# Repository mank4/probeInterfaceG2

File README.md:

# probeInterfaceG2

probeInterfaceG2 is a USB controlled interface box for transmission and reception of digital signals on 12-pins of a 14-pin flat band cable. The pin number layout is common with [GGB Picoprobe multi-contact wedge probes](https://ggb.com/home/multi-contact-wedges/). It features galvanically isolated USB for control, adjustable logic levels from 0.65 to 3.3 V and relays for disabling unused pins. The device is controlled via IEEE 488.2 compatible SCPI commands.

Currently the following interfaces are supported:
- GPIO
- SPI

probeInterfaceG2 is licensed under GPL v3. As the case's 3D model is assumed to be (c) Hammond Manufacturing Ltd., originally obtained from https://www.hammfg.com/electronics/small-case/extruded/1455#product-tables, a script is included to download the model.

probeInterfaceG2 uses
- [tinyusb](https://github.com/hathach/tinyusb)
- [scpi-parser](https://github.com/j123b567/scpi-parser)

## Hardware Features

- Raspberry RP2040 microcontroller
  - pio cells for high-speed, unconstraint muxable IO functions
  - integrated USB for programming and IEEE 488.2 SCPI control
- 0.65V - 3.3V level shifters
  - Controllable common logic level by discrete 12-bit R-2R DAC or external input
- Relays for enabling/disabling IOs

## SCPI commands

Pin numbering is based on [GGB Picoprobe multi-contact wedge probes](https://ggb.com/home/multi-contact-wedges/) numbering scheme.

__*IDN?__

Returns device type.

__*RST__

Resets settings made and clears error.

__*CLS__

Clears error. Device stores only a single error.

__:SYSTem:ERRor[:NEXT]?__

Returns <errorNumber>,<errorDescription> as described by [Keysight](https://na.support.keysight.com/pna/help/latest/Support/SCPI_Errors.htm) and clears error.

__:SYSTem:ERRor:COUNt?__

Returns number of errors.

__:SYSTem:VERSion?__

Returns system version number.

__ECHO `<text>`__

Echos argument.

__BOOTSEL__

Reboots the pin in bootloader mode.

__IO:LEVel `<V>`__

Sets the IO level voltage.

__IO<1:12>:FUnc `<IN|OUT|CS|SCK|MISO|MOSI>`__

Sets the pins function to one of the following. IN and OUT can be used multiple times while the SPI related functions can only be used once. Pins are left in last configuration when changing SPI related functions from one pin to another. This function does not enable the according output relay.

__IO<1:12>:ENable <1|0>__

Enables or disables the relay of the corresponding IO pin.

__IO<1:12>:WRite <1|0>__

Sets an OUT configured pin high or low.

__IO<1:12>:REad__

Reads an IN configured pin and returns 0 or 1.

__SPI:TRANSfer? <binary values>__

Writes the given bytes to the SPI bus using the configured settings and returns the response of MISO as binary values.

__SPI:CPHA <1|0>__

Sets the Clock phase (CPHA) to the corresponding value.

__SPI:CPOL <1|0>__

Sets the Clock polarity (CPOL) to the corresponding value.

__SPI:BAUDrate <MHz>__

Speed of the probes SPI interface is set to defined float value in MHz.

__SPI:BAUDrate?__

Reads the speed of the currently configured baudrate as float in MHz.

## RP2040 toolchain

Assuming Windows or Ubuntu/Debian the following setup is required for compiling the firmware. For normal use this is not required, VISA drivers (on Windows) are sufficient for common use.

- Only on windows: Install WSL / Ubuntu on Windows, run `sudo apt update`
- Make sure the following packages exist: `sudo apt install cmake gcc-arm-none-eabi libnewlib-arm-none-eabi libstdc++-arm-none-eabi-newlib git build-essential`
- Clone dependencies: `git submodule init` and `git submodule update`
- Clone the [pico-sdk](https://github.com/raspberrypi/pico-sdk) into the same folder as probeInterfaceG2 and update submodules if requested by cmake in the next steps
- Create build folder in firmware and cd into. `cd fw && mkdir build && cd build`
- Then run `export PICO_SDK_PATH=../../../pico-sdk` and `cmake ..`
- Then `make -j4` (4 is the number of cores used for compilation)
- If compilation fails with USB descriptor length errors, do the following: cd into pico-sdk folder and `cd lib/tinyusb/` and then `git pull origin master`
- On Windows and Linux: Copy the uf2 onto the mass storage of the RP2040. Bootloader mode is entered by pressing the button while plugging in.
- With correctly set up udev rules: Run `../load.sh` with the RP2040 connected via USB. When not running the probeInterfaceG2 firmware ress the button while pluggin in. [udev rules](https://gist.github.com/alejoseb/c7a7b4c67f0cf665dadabb26a5a87597) for the probeInterfaceG2:
```
/etc/udev/rules.d/99-probeInterfaceG2.rules
SUBSYSTEMS=="usb", ACTION=="add", ATTRS{idVendor}=="16c0", ATTRS{idProduct}=="03e8",  MODE="0666", GROUP="usbtmc"
```

For programming hints see the [Getting started](https://datasheets.raspberrypi.com/pico/getting-started-with-pico.pdf) guide.

## Possible improvements

- Better 3.3 V overvoltage protection circuit currently realized using X0202NN
- Ethernet interface VXI11
- Integrated power supply for DUT, with high precision measurement functions and grounding feature

## Resources

- Frontend
  - Agilent E3631 Service Guide
  - HP 6114A Service Guide
  - Power Designs 5020 Service Guide
  - The Art of Electronics by Horowitz
- Microcontroller
  - [RP2040](https://www.raspberrypi.com/documentation/microcontrollers/rp2040.html), [Pi pico](https://www.raspberrypi.com/products/raspberry-pi-pico/), RP2040 Minimal Kicad reference design
  - [SCPI specifications](https://www.ivifoundation.org/specifications/default.aspx), [SCPI-99 standard](https://www.ivifoundation.org/docs/scpi-99.pdf), [SCPI library](https://github.com/j123b567/scpi-parser)
  - [tinyusb for usbtmc](https://github.com/hathach/tinyusb), [example](https://github.com/markb139/pico_logic)
- Ethernet
  - Wiznet w5500 [eval](https://www.wiznet.io/product-item/w5500-evb-pico/) [doc](https://docs.wiznet.io/Product/iEthernet/W5500/w5500-evb-pico)

## Acknowledgement

The financial support by the Federal Ministry of Education and Research of Germany in the project "Open6GHub" (grant number: 16KISK005) is acknowledged.

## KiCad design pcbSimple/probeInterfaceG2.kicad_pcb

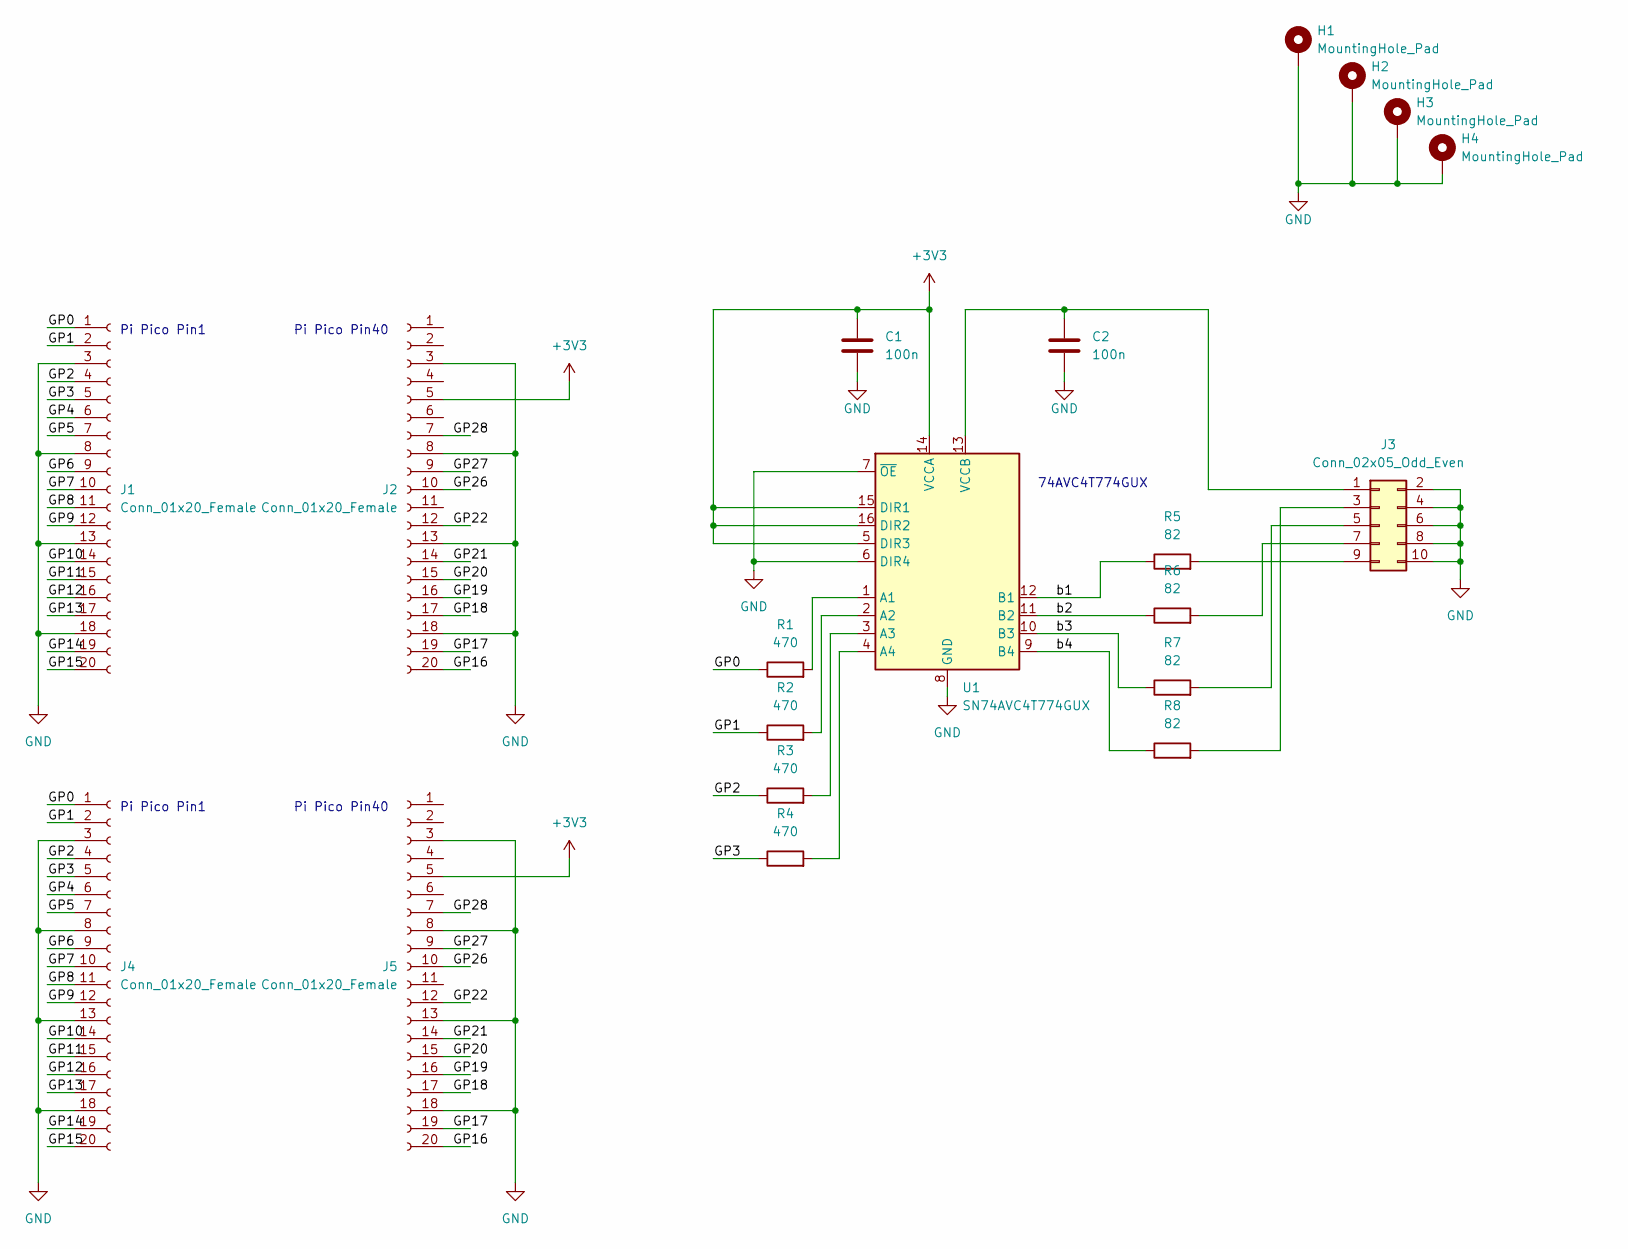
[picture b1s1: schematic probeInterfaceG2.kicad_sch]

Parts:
C1, C2: 100n; C_0402_1005Metric
H1, H2, H3, H4: MountingHole_Pad; MountingHole_3.2mm_M3_DIN965_Pad
J1, J2, J4, J5: Conn_01x20_Female; PinSocket_1x20_P2.54mm_Vertical
J3: Conn_02x05_Odd_Even; PinHeader_2x05_P2.54mm_Vertical
R1, R2, R3, R4: 470; R_0402_1005Metric
R5, R6, R7, R8: 82; R_0402_1005Metric
U1: SN74AVC4T774GUX; XQFN16

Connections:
+3V3: C1.1, J2.5, J5.5, U1.5 (DIR3), U1.14 (VCCA), U1.15 (DIR1), U1.16 (DIR2)
/GP0: J1.1, J4.1, R1.1
/GP1: J1.2, J4.2, R2.1
/GP2: J1.4, J4.4, R3.1
/GP3: J1.5, J4.5, R4.1
/GP4: J1.6, J4.6
/GP5: J1.7, J4.7
/GP6: J1.9, J4.9
/GP7: J1.10, J4.10
/GP8: J1.11, J4.11
/GP9: J1.12, J4.12
/GP10: J1.14, J4.14
/GP11: J1.15, J4.15
/GP12: J1.16, J4.16
/GP13: J1.17, J4.17
/GP14: J1.19, J4.19
/GP15: J1.20, J4.20
/GP16: J2.20, J5.20
/GP17: J2.19, J5.19
/GP18: J2.17, J5.17
/GP19: J2.16, J5.16
/GP20: J2.15, J5.15
/GP21: J2.14, J5.14
/GP22: J2.12, J5.12
/GP26: J2.10, J5.10
/GP27: J2.9, J5.9
/GP28: J2.7, J5.7
/b1: R5.1, U1.12 (B1)
/b2: R6.1, U1.11 (B2)
/b3: R7.1, U1.10 (B3)
unnamed: C2.1, J3.1, U1.13 (VCCB)
unnamed: J3.3, R8.2
unnamed: J3.5, R7.2
unnamed: J3.7, R6.2
unnamed: J3.9, R5.2
unnamed: R1.2, U1.1 (A1)
unnamed: R2.2, U1.2 (A2)
unnamed: R3.2, U1.3 (A3)
unnamed: R4.2, U1.4 (A4)

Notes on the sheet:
Pi Pico Pin40
Pi Pico Pin1
74AVC4T774GUX

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
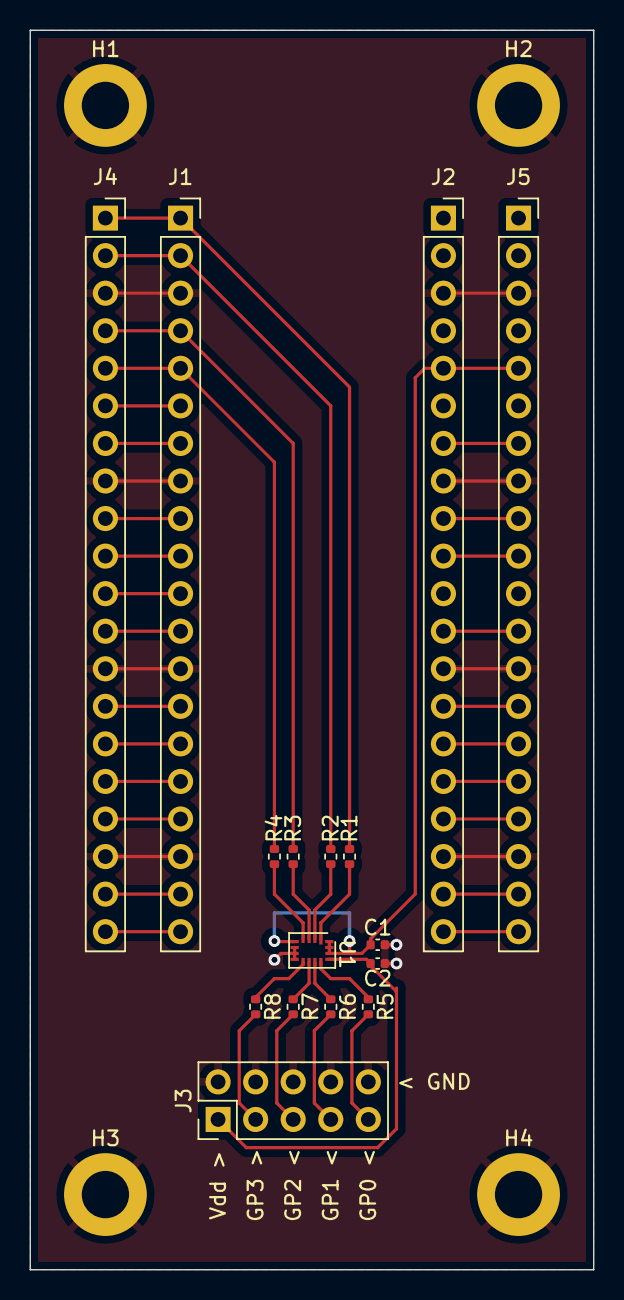
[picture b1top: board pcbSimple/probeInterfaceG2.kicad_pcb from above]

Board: 2 copper layers, 38.1 x 83.8 mm, 20 parts (0 on the bottom side), 41 nets.

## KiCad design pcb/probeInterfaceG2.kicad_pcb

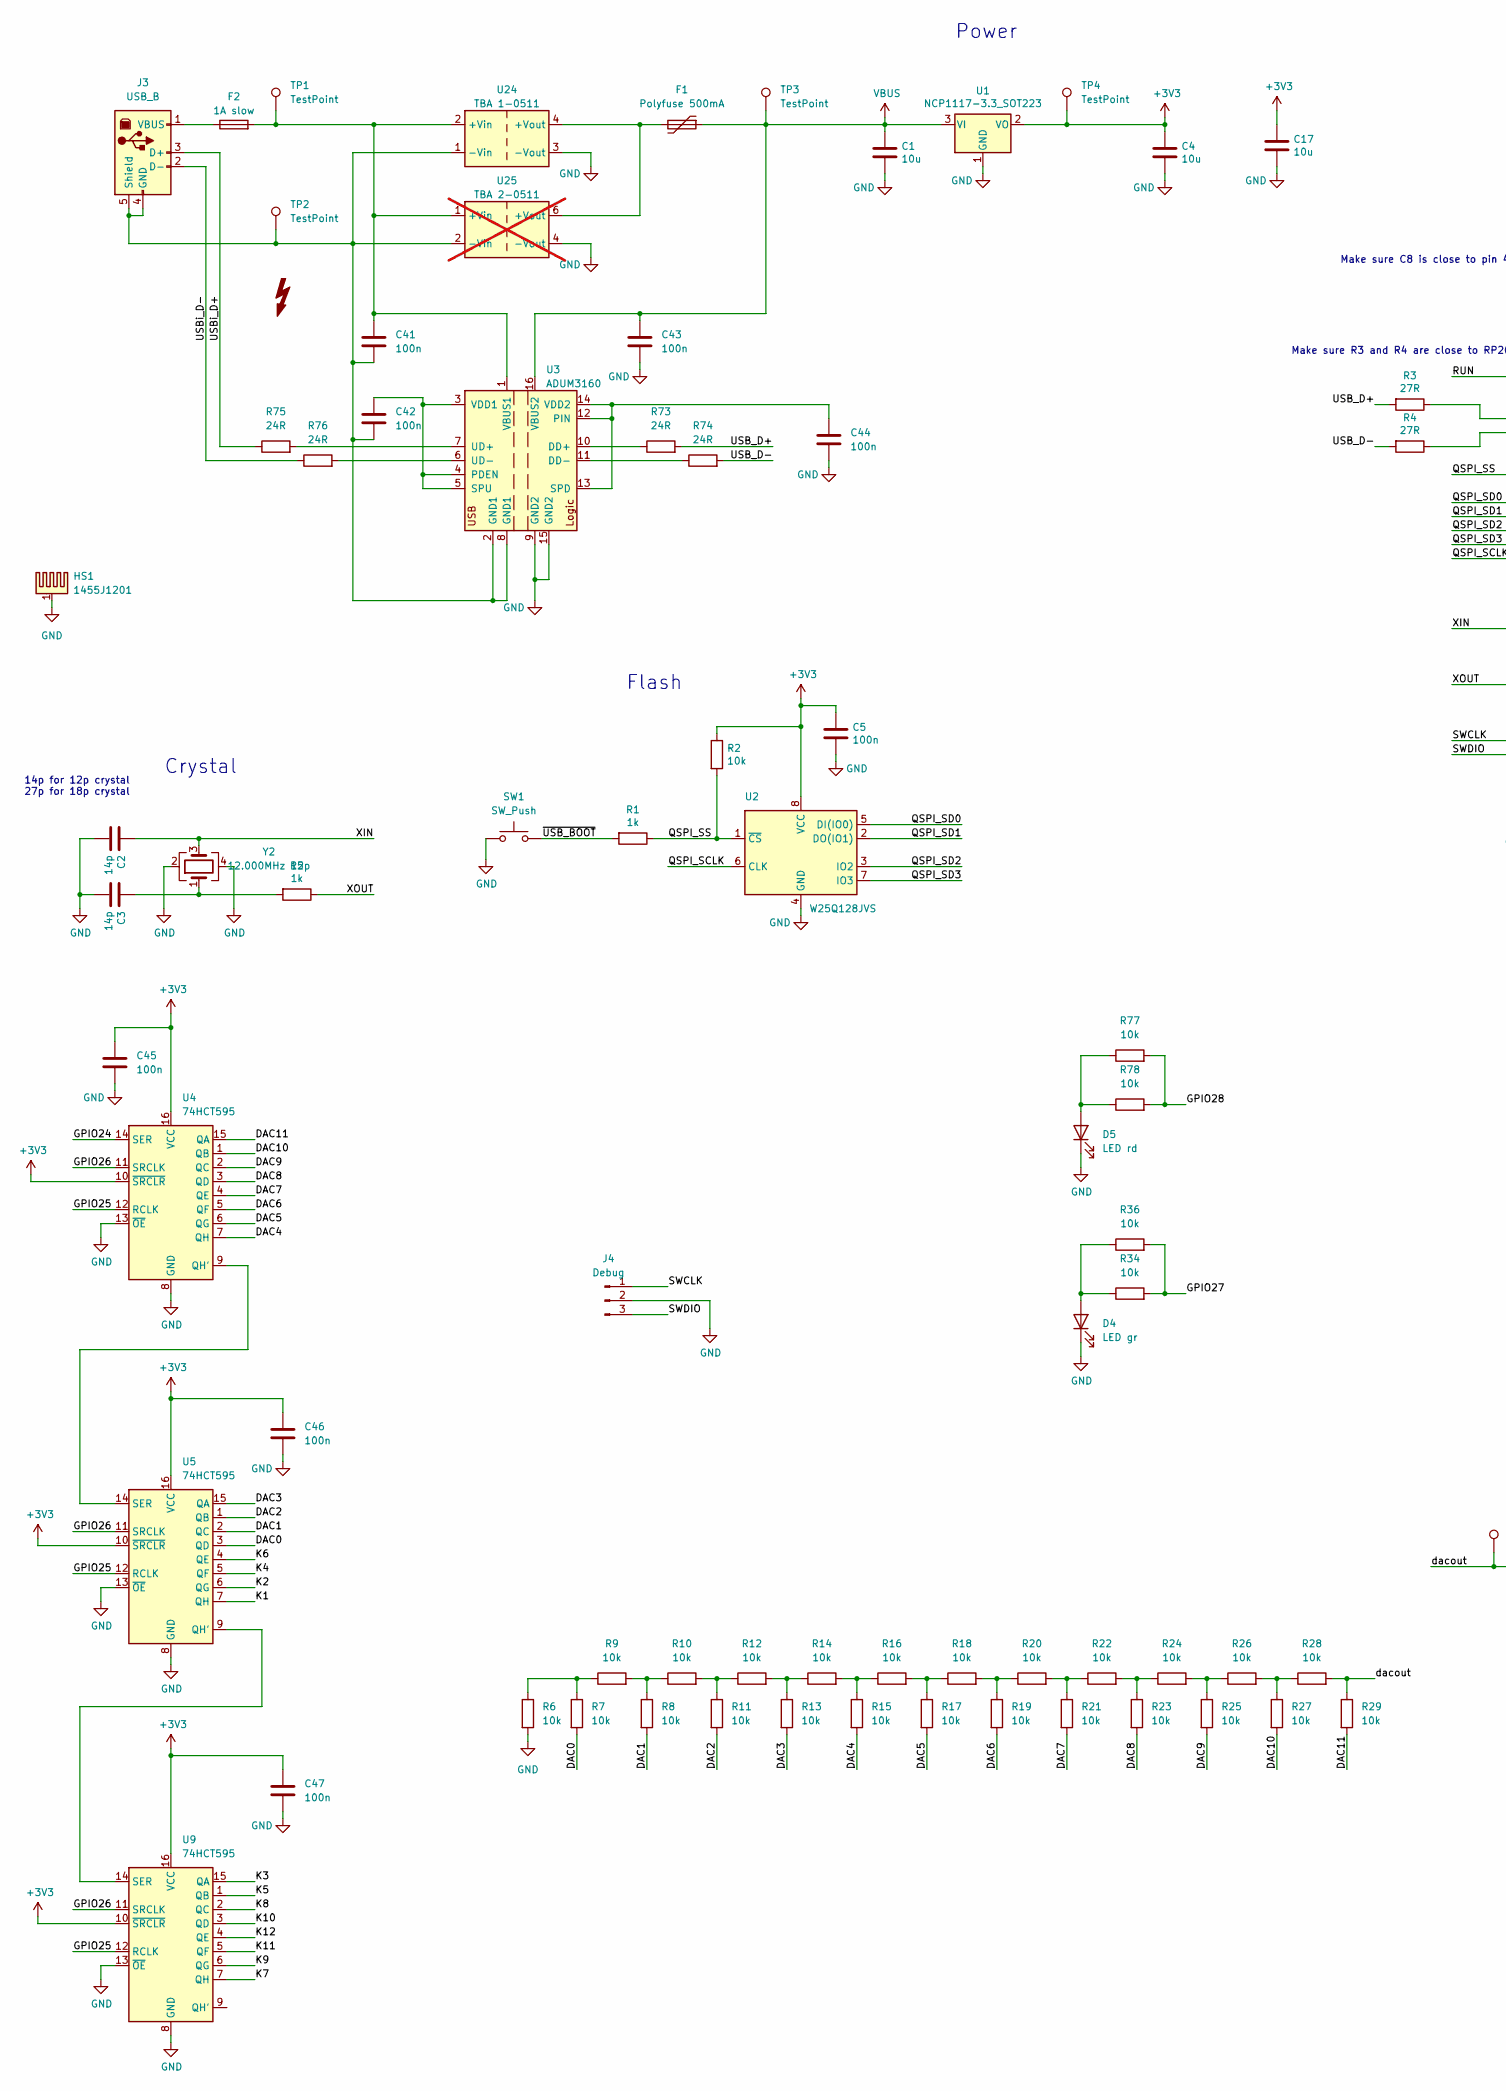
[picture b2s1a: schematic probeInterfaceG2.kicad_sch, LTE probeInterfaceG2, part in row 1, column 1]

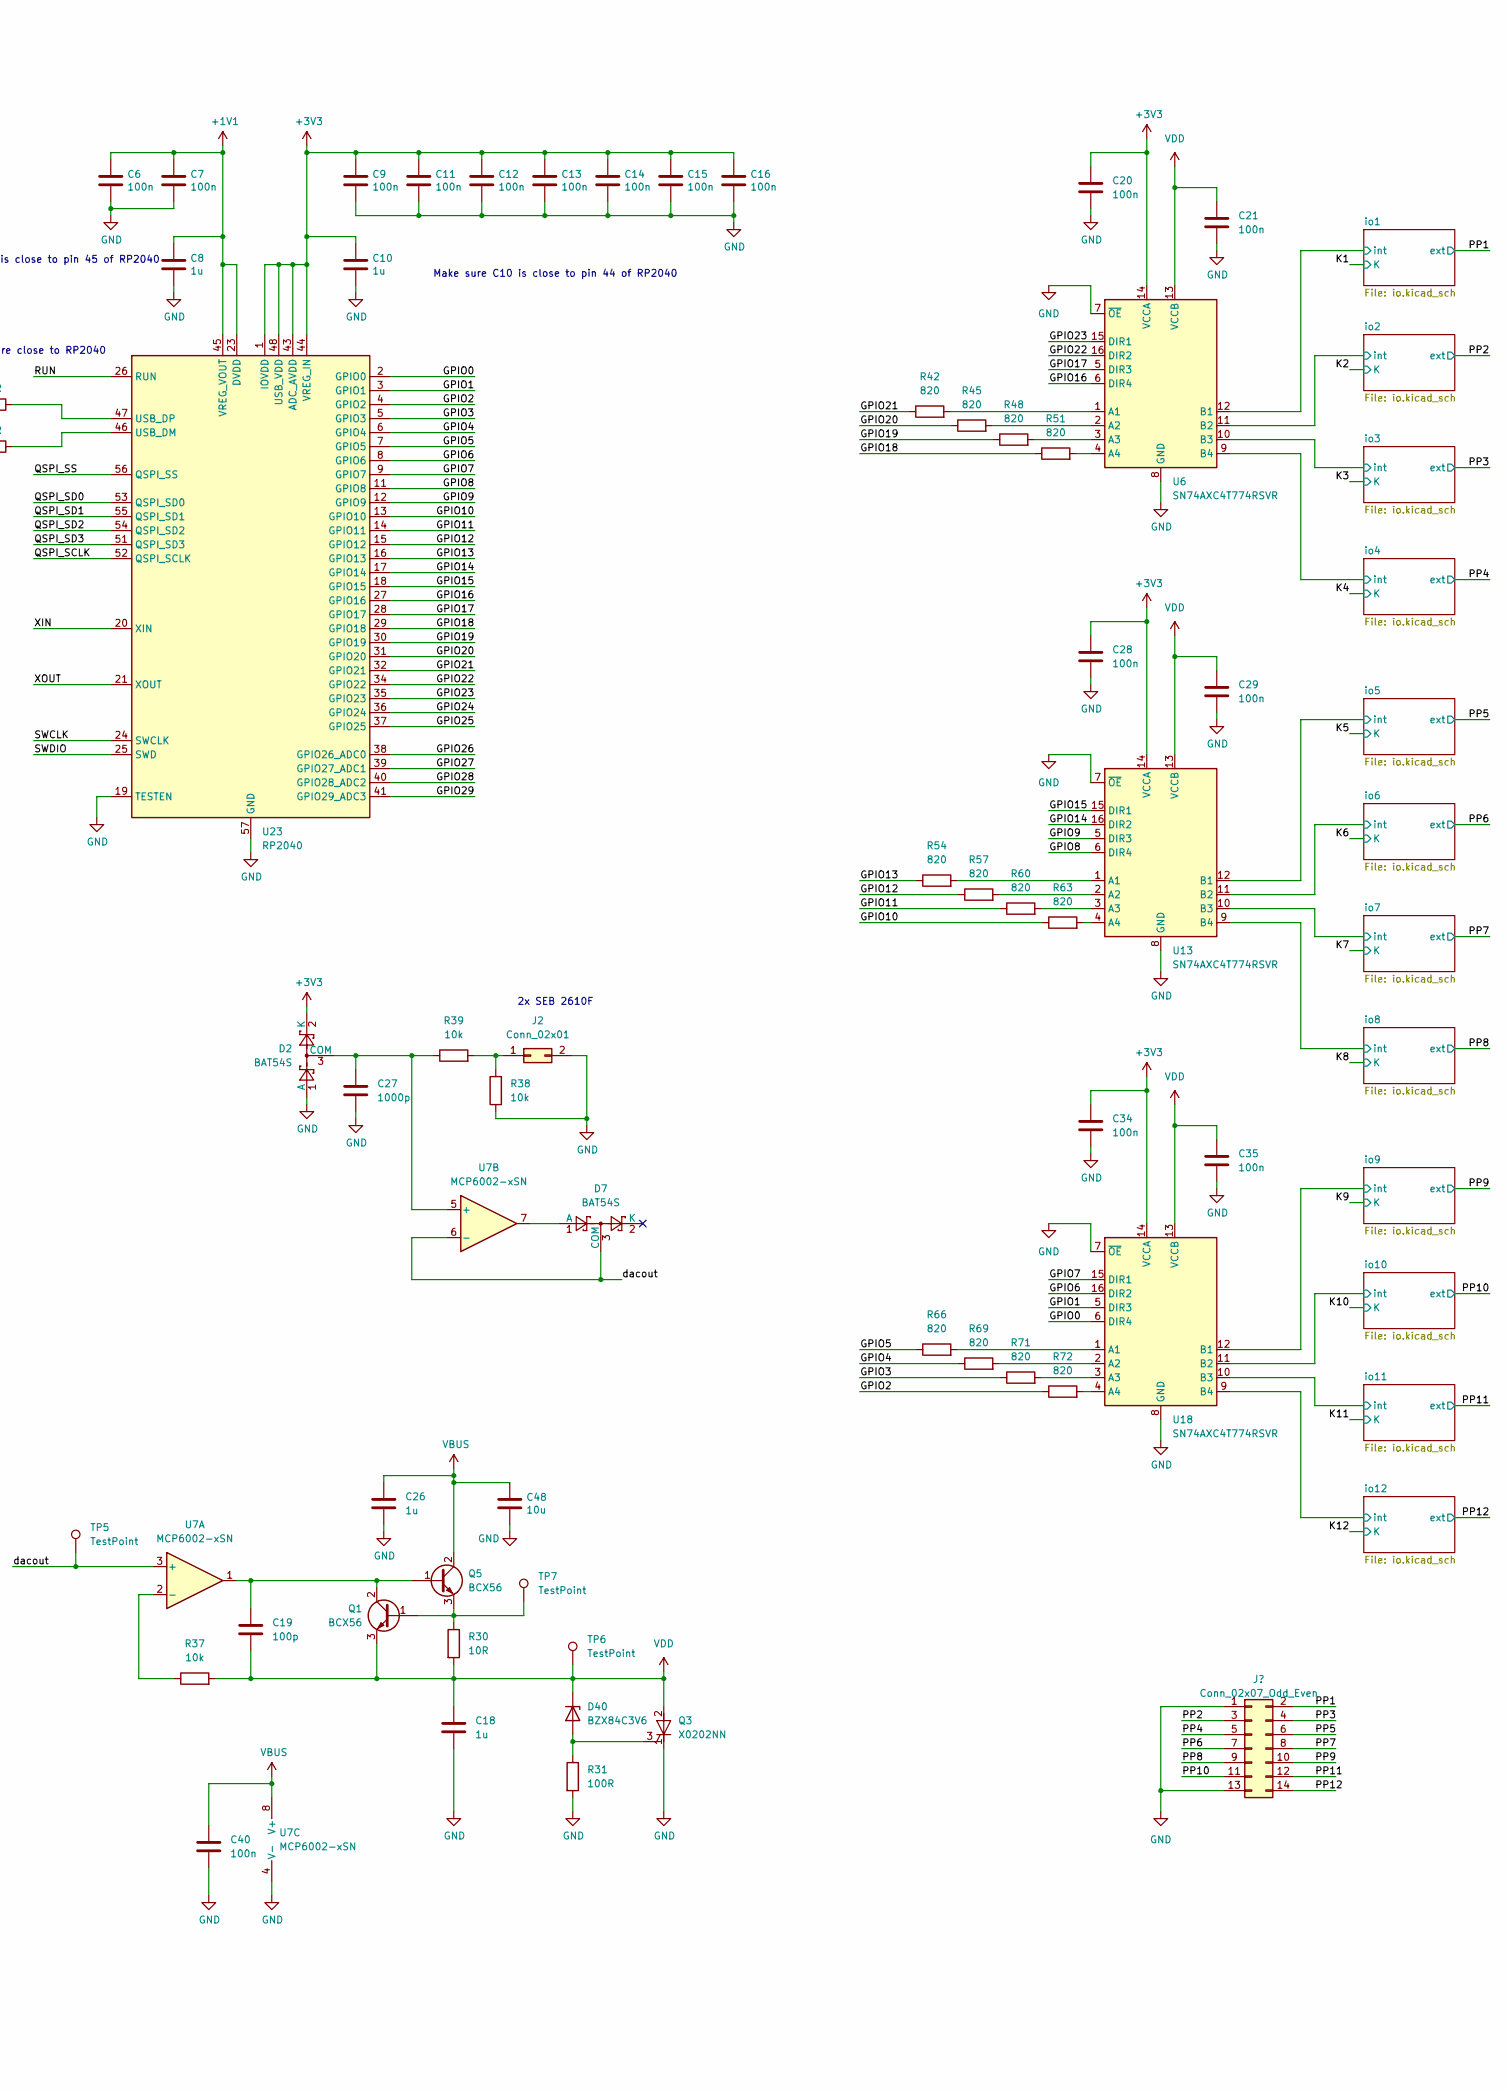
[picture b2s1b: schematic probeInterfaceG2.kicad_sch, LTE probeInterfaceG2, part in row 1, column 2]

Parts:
C1, C4, C17, C48: 10u; C_0805_2012Metric; Digikey 1276-1096-1-ND
C2, C3: 14p; C_0402_1005Metric; Digikey 13-CC0402JPNPO9BN180DKR-ND
C5, C6, C7, C9, C11, C12, C13, C14, C15, C16, C20, C21, C28, C29, C34, C35, C40, C41, C42, C43, C44, C45, C46, C47: 100n; C_0402_1005Metric; Digikey 1276-1043-1-ND
C8, C10, C18, C26: 1u; C_0402_1005Metric; Digikey 1276-1076-1-ND
C19: 100p; C_0402_1005Metric; Digikey 13-CC0402JPNPO9BN101DKR-ND
C27: 1000p; C_0402_1005Metric; Digikey 490-GCM1555C1H102GA16JDKR-ND
D2, D7: BAT54S; SOT-23; Digikey BAT54SLT1GOSDKR-ND
D4: LED gr; LED_0402_1005Metric; Digikey 754-1101-1-ND
D5: LED rd; LED_0402_1005Metric; Digikey 754-1104-1-ND
D40: BZX84C3V6; SOT-23; Digikey BZX84C3V6LT1GOSDKR-ND
F1: Polyfuse 500mA; Fuse_1206_3216Metric; Digikey 0ZCJ0050FF2G
F2: 1A slow; Fuse_1206_3216Metric; Digikey 507-1891-1-ND
HS1: 1455J1201; Digikey HM890-ND
J1: Conn_02x07_Odd_Even; IDC-Header_2x07_P2.54mm_Horizontal; Digikey S9028-ND
J2: Conn_02x01; PinSocket_1x02_P2.54mm_Vertical
J3: USB_B; USB_B_OST_USB-B1HSxx_Horizontal; Digikey 102-3999-ND
J4: Debug; PinHeader_1x03_P2.54mm_Vertical
Q1, Q5: BCX56; SOT-89-3; Digikey 1727-2930-1-ND
Q3: X0202NN; SOT-223; Digikey 497-7697-1-ND
R1, R5: 1k; C_0402_1005Metric; Digikey 13-AC0402FR-131KLDKR-ND
R2, R6, R7, R8, R9, R10, R11, R12, R13, R14, R15, R16, R17, R18, R19, R20, R21, R22, R23, R24, R25, R26, R27, R28, R29, R34, R36, R37, R38, R39, R77, R78: 10k; R_0402_1005Metric; Digikey YAG3436CT-ND
R3, R4: 27R; R_0402_1005Metric; Digikey YAG3086CT-ND
R30: 10R; R_0805_2012Metric; Digikey 13-RC0402FR-1310RLDKR-ND
R31: 100R; R_0402_1005Metric; Digikey YAG3435CT-ND
R42, R45, R48, R51, R54, R57, R60, R63, R66, R69, R71, R72: 820; R_0402_1005Metric; Digikey 311-820LRCT-ND
R73, R74, R75, R76: 24R; R_0402_1005Metric; Digikey YAG3073CT-ND
SW1: SW_Push; SW_Tactile_SPST_Angled_PTS645Vx58-2LFS; Digikey PTS645VM58-2 LFS
SYM1: SYM_Flash_Small; Symbol_Highvoltage_Type1_CopperTop_Small
TP1, TP2, TP3, TP4, TP5, TP6, TP7: TestPoint; TestPoint_Bridge_Pitch2.54mm_Drill1.0mm
U1: NCP1117-3.3_SOT223; SOT-223-3_TabPin2; Digikey AZ1117IH-3.3TRG1DIDKR-ND
U2: W25Q128JVS; SOIC-8_5.23x5.23mm_P1.27mm; Digikey W25Q128JVSIQDKR-ND
U3: ADUM3160; SOIC-16W_7.5x10.3mm_P1.27mm; Digikey ADUM3160BRWZ-RLDKR-ND
U4, U5, U9: 74HCT595; SO-16_3.9x9.9mm_P1.27mm; Digikey 1727-2821-1-ND
U6, U13, U18: SN74AXC4T774RSVR; XQFN16; Digikey 296-SN74AXC4T774RSVRDKR-ND
U7: MCP6002-xSN; SOIC-8_3.9x4.9mm_P1.27mm; Digikey MCP6002-I/SN-ND
U23: RP2040; QFN-56-1EP_7x7mm_P0.4mm_EP3.2x3.2mm; Digikey 2648-SC0914(13)DKR-ND
U24: TBA 1-0511; Converter_DCDC_Murata_CRE1xxxxxx3C_THT; Digikey 1951-3369-ND
U25: TBA 2-0511; Converter_DCDC_TRACO_TMR-1-xxxx_Single_THT; Digikey 1951-3429-ND; not fitted
Y2: 12.000MHz 12p; Crystal_SMD_Abracon_ABM3B-4Pin_5.0x3.2mm; Digikey ABM3B-12.000MHZ-12-N2Y-T

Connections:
+1V1: C6.1, C7.1, C8.1, U23.23 (DVDD), U23.45 (VREG_VOUT), U23.50 (DVDD)
+3V3: C4.1, C5.1, C9.1, C10.1, C11.1, C12.1, C13.1, C14.1, C15.1, C16.1, C17.1, C20.1, C28.1, C34.1, C45.1, C46.1, C47.1, D2.2 (K), R2.1, TP4.1, U1.2 (VO), U2.8 (VCC), U4.10 (~SRCLR), U4.16 (VCC), U5.10 (~SRCLR), U5.16 (VCC), U6.14 (VCCA), U9.10 (~SRCLR), U9.16 (VCC), U13.14 (VCCA), U18.14 (VCCA), U23.1 (IOVDD), U23.10 (IOVDD), U23.22 (IOVDD), U23.33 (IOVDD), U23.42 (IOVDD), U23.43 (ADC_AVDD), U23.44 (VREG_IN), U23.48 (USB_VDD), U23.49 (IOVDD)
/DAC0: R7.2, U5.3 (QD)
/DAC1: R8.2, U5.2 (QC)
/DAC2: R11.2, U5.1 (QB)
/DAC3: R13.2, U5.15 (QA)
/DAC4: R15.2, U4.7 (QH)
/DAC5: R17.2, U4.6 (QG)
/DAC6: R19.2, U4.5 (QF)
/DAC7: R21.2, U4.4 (QE)
/DAC8: R23.2, U4.3 (QD)
/DAC9: R25.2, U4.2 (QC)
/DAC10: R27.2, U4.1 (QB)
/DAC11: R29.2, U4.15 (QA)
/GPIO0: U18.6 (DIR4), U23.2 (GPIO0)
/GPIO1: U18.5 (DIR3), U23.3 (GPIO1)
/GPIO2: R72.1, U23.4 (GPIO2)
/GPIO3: R71.1, U23.5 (GPIO3)
/GPIO4: R69.1, U23.6 (GPIO4)
/GPIO5: R66.1, U23.7 (GPIO5)
/GPIO6: U18.16 (DIR2), U23.8 (GPIO6)
/GPIO7: U18.15 (DIR1), U23.9 (GPIO7)
/GPIO8: U13.6 (DIR4), U23.11 (GPIO8)
/GPIO9: U13.5 (DIR3), U23.12 (GPIO9)
/GPIO10: R63.1, U23.13 (GPIO10)
/GPIO11: R60.1, U23.14 (GPIO11)
/GPIO12: R57.1, U23.15 (GPIO12)
/GPIO13: R54.1, U23.16 (GPIO13)
/GPIO14: U13.16 (DIR2), U23.17 (GPIO14)
/GPIO15: U13.15 (DIR1), U23.18 (GPIO15)
/GPIO16: U6.6 (DIR4), U23.27 (GPIO16)
/GPIO17: U6.5 (DIR3), U23.28 (GPIO17)
/GPIO18: R51.1, U23.29 (GPIO18)
/GPIO19: R48.1, U23.30 (GPIO19)
/GPIO20: R45.1, U23.31 (GPIO20)
/GPIO21: R42.1, U23.32 (GPIO21)
/GPIO22: U6.16 (DIR2), U23.34 (GPIO22)
/GPIO23: U6.15 (DIR1), U23.35 (GPIO23)
/GPIO24: U4.14 (SER), U23.36 (GPIO24)
/GPIO25: U4.12 (RCLK), U5.12 (RCLK), U9.12 (RCLK), U23.37 (GPIO25)
/GPIO26: U4.11 (SRCLK), U5.11 (SRCLK), U9.11 (SRCLK), U23.38 (GPIO26_ADC0)
/GPIO27: R34.2, R36.2, U23.39 (GPIO27_ADC1)
/GPIO28: R77.2, R78.2, U23.40 (GPIO28_ADC2)
/GPIO29: U23.41 (GPIO29_ADC3)
/K3: U9.15 (QA); also elsewhere on the board
/K4: U5.5 (QF); also elsewhere on the board
/K5: U9.1 (QB); also elsewhere on the board
/K6: U5.4 (QE); also elsewhere on the board
/K7: U9.7 (QH); also elsewhere on the board
/K8: U9.2 (QC); also elsewhere on the board
/K9: U9.6 (QG); also elsewhere on the board
/K10: U9.3 (QD); also elsewhere on the board
/K11: U9.5 (QF); also elsewhere on the board
/K12: U9.4 (QE); also elsewhere on the board
/PP1: J1.2; also elsewhere on the board
/PP2: J1.3; also elsewhere on the board
/PP3: J1.4; also elsewhere on the board
/PP4: J1.5; also elsewhere on the board
/PP5: J1.6; also elsewhere on the board
/PP6: J1.7; also elsewhere on the board
/PP7: J1.8; also elsewhere on the board
/PP8: J1.9; also elsewhere on the board
/PP9: J1.10; also elsewhere on the board
/PP10: J1.11; also elsewhere on the board
/PP11: J1.12; also elsewhere on the board
/PP12: J1.14; also elsewhere on the board
/QSPI_SCLK: U2.6 (CLK), U23.52 (QSPI_SCLK)
/QSPI_SD0: U2.5 (DI(IO0)), U23.53 (QSPI_SD0)
/QSPI_SD1: U2.2 (DO(IO1)), U23.55 (QSPI_SD1)
/QSPI_SD2: U2.3 (IO2), U23.54 (QSPI_SD2)
/QSPI_SD3: U2.7 (IO3), U23.51 (QSPI_SD3)
/QSPI_SS: R1.1, R2.2, U2.1 (~CS), U23.56 (QSPI_SS)
/RUN: U23.26 (RUN)
/SWCLK: J4.1, U23.24 (SWCLK)
/SWDIO: J4.3, U23.25 (SWD)
/USB_D+: R3.2, R73.2
/USB_D-: R4.2, R74.2
/USBi_D+: J3.3 (D+), R75.1
/USBi_D-: J3.2 (D-), R76.1
/XIN: C2.1, U23.20 (XIN), Y2.3
/XOUT: R5.1, U23.21 (XOUT)
/dacout: D7.3 (COM), R28.2, R29.1, TP5.1, U7.3 (+), U7.6 (-)
/io1/int: U6.12 (B1); also elsewhere on the board
/io2/int: U6.11 (B2); also elsewhere on the board
/io3/int: U6.10 (B3); also elsewhere on the board
/io5/int: U13.12 (B1); also elsewhere on the board
/io6/int: U13.11 (B2); also elsewhere on the board
/io7/int: U13.10 (B3); also elsewhere on the board
/io9/int: U18.12 (B1); also elsewhere on the board
/io10/int: U18.11 (B2); also elsewhere on the board
/io11/int: U18.10 (B3); also elsewhere on the board
/~USB_BOOT: R1.2, SW1.2
unnamed: C3.1, R5.2, Y2.1
unnamed: C27.1, D2.3 (COM), R39.1, U7.5 (+)
unnamed: D4.2 (A), R34.1, R36.1
unnamed: D5.2 (A), R77.1, R78.1
unnamed: D7.1 (A), U7.7
unnamed: D40.1 (A), Q3.3 (G), R31.1
unnamed: J2.1, R38.2, R39.2
unnamed: C41.2, C42.2, J3.4 (GND), J3.5 (Shield), TP2.1, U3.2 (GND1), U3.8 (GND1), U24.1 (-Vin), U25.2 (-Vin)
unnamed: F2.1, J3.1 (VBUS)
unnamed: Q1.1 (B), Q5.3 (E), R30.1, TP7.1
unnamed: C19.1, Q1.2 (C), Q5.1 (B), U7.1
unnamed: R6.1, R7.1, R9.1
unnamed: R8.1, R9.2, R10.1
unnamed: R10.2, R11.1, R12.1
unnamed: R12.2, R13.1, R14.1
unnamed: R14.2, R15.1, R16.1
unnamed: R16.2, R17.1, R18.1
unnamed: R18.2, R19.1, R20.1
unnamed: R20.2, R21.1, R22.1
unnamed: R22.2, R23.1, R24.1
unnamed: R24.2, R25.1, R26.1
unnamed: R26.2, R27.1, R28.1
unnamed: R73.1, U3.10 (DD+)
unnamed: R74.1, U3.11 (DD-)
unnamed: C42.1, U3.3 (VDD1), U3.4 (PDEN), U3.5 (SPU)
unnamed: C44.1, U3.12 (PIN), U3.13 (SPD), U3.14 (VDD2)
unnamed: R75.2, U3.7 (UD+)
unnamed: R76.2, U3.6 (UD-)
unnamed: U4.9 (QH'), U5.14 (SER)
unnamed: U5.9 (QH'), U9.14 (SER)
unnamed: R42.2, U6.1 (A1)
unnamed: R45.2, U6.2 (A2)
unnamed: R48.2, U6.3 (A3)
unnamed: R51.2, U6.4 (A4)
unnamed: R37.1, U7.2 (-)
unnamed: R54.2, U13.1 (A1)
unnamed: R57.2, U13.2 (A2)
unnamed: R60.2, U13.3 (A3)
unnamed: R63.2, U13.4 (A4)
unnamed: R66.2, U18.1 (A1)
unnamed: R69.2, U18.2 (A2)
unnamed: R71.2, U18.3 (A3)
unnamed: R72.2, U18.4 (A4)
unnamed: R4.1, U23.46 (USB_DM)
unnamed: R3.1, U23.47 (USB_DP)
unnamed: C41.1, F2.2, TP1.1, U3.1 (VBUS1), U24.2 (+Vin), U25.1 (+Vin)
unnamed: F1.2, U24.4 (+Vout), U25.6 (+Vout)
VBUS: C1.1, C26.1, C40.1, C43.1, C48.1, F1.1, Q5.2 (C), TP3.1, U1.3 (VI), U3.16 (VBUS2), U7.8 (V+); also elsewhere on the board
VDD: C18.1, C19.2, C21.1, C29.1, C35.1, D40.3 (K), Q1.3 (E), Q3.2 (A), Q3.4 (A), R30.2, R37.2, TP6.1, U6.13 (VCCB), U13.13 (VCCB), U18.13 (VCCB); also elsewhere on the board

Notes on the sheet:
2x SEB 2610F
Make sure C8 is close to pin 45 of RP2040
Power
Make sure C10 is close to pin 44 of RP2040
Make sure R3 and R4 are close to RP2040
14p for 12p crystal 27p for 18p crystal
Flash
Crystal

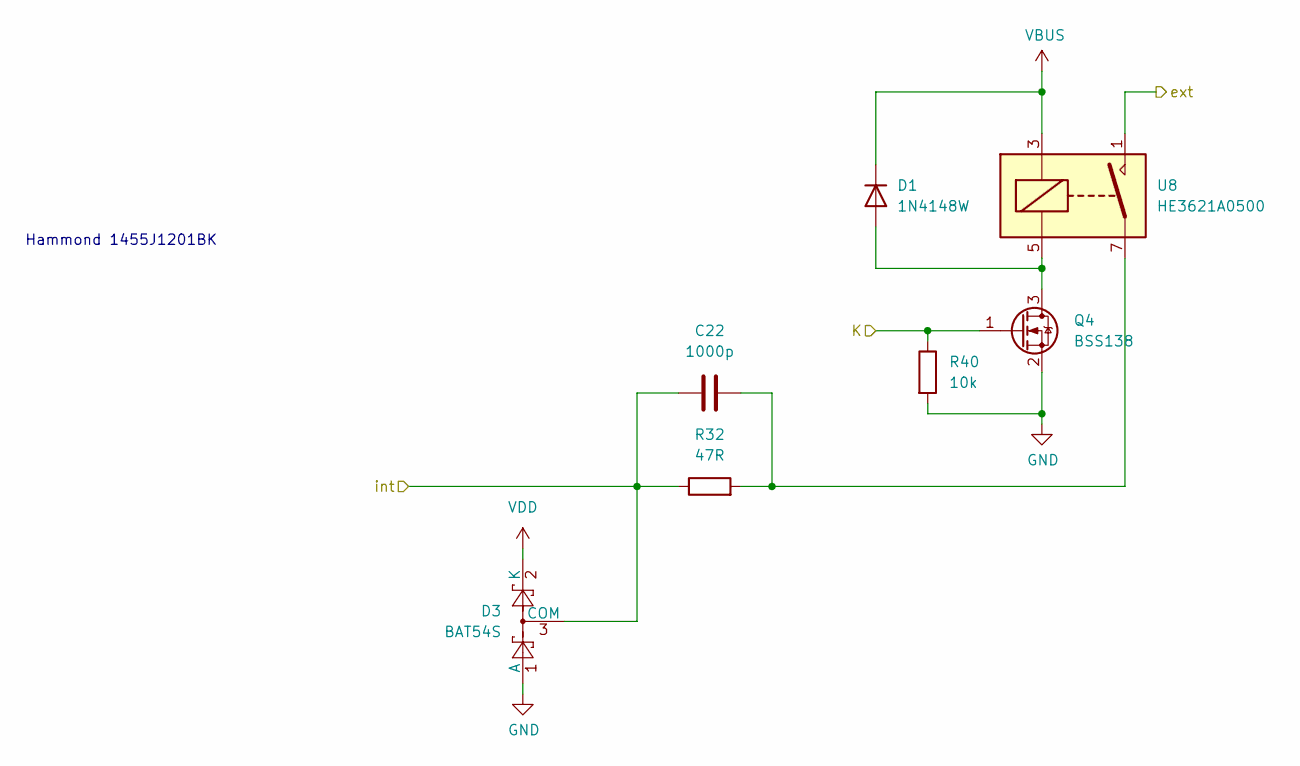
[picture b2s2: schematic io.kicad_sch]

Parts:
C22: 1000p; C_0402_1005Metric; Digikey 490-GCM1555C1H102GA16JDKR-ND
D1: 1N4148W; D_SOD-123; Digikey 4878-1N4148WDKR-ND
D3: BAT54S; SOT-23; Digikey BAT54SLT1GOSDKR-ND
Q4: BSS138; SOT-23; Digikey 1727-1143-1-ND
R32: 47R; R_0402_1005Metric; Digikey 311-47.0LRCT-ND
R40: 10k; R_0402_1005Metric; Digikey YAG3436CT-ND
U8: HE3621A0500; Relay_SPST_StandexMeder_SIL_Form1A; Digikey HE206-ND

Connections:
/PP1: U8.1; also elsewhere on the board
/io1/int: C22.1, D3.3 (COM), R32.1; also elsewhere on the board
unnamed: C22.2, R32.2, U8.7
VBUS: D1.1 (K), U8.3; also elsewhere on the board
VDD: D3.2 (K); also elsewhere on the board

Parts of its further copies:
C23, C24, C25, C30, C31, C32, C33, C36, C37, C38, C39: 1000p; C_0402_1005Metric; Digikey 490-GCM1555C1H102GA16JDKR-ND
D6, D10, D13, D16, D19, D22, D25, D28, D31, D34, D37: BAT54S; SOT-23; Digikey BAT54SLT1GOSDKR-ND
D41, D42, D43, D44, D45, D46, D47, D48, D49, D50, D51: 1N4148W; D_SOD-123; Digikey 4878-1N4148WDKR-ND
Q2, Q6, Q7, Q8, Q9, Q10, Q11, Q12, Q13, Q14, Q15: BSS138; SOT-23; Digikey 1727-1143-1-ND
R33, R41, R44, R47, R50, R53, R56, R59, R62, R65, R68: 47R; R_0402_1005Metric; Digikey 311-47.0LRCT-ND
R35, R43, R46, R49, R52, R55, R58, R61, R64, R67, R70: 10k; R_0402_1005Metric; Digikey YAG3436CT-ND
U10, U11, U12, U14, U15, U16, U17, U19, U20, U21, U22: HE3621A0500; Relay_SPST_StandexMeder_SIL_Form1A; Digikey HE206-ND

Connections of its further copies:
/K3: Q6.1 (G), R43.1; also elsewhere on the board
/K4: Q7.1 (G), R46.1; also elsewhere on the board
/K5: Q8.1 (G), R49.1; also elsewhere on the board
/K6: Q9.1 (G), R52.1; also elsewhere on the board
/K7: Q10.1 (G), R55.1; also elsewhere on the board
/K8: Q11.1 (G), R58.1; also elsewhere on the board
/K9: Q12.1 (G), R61.1; also elsewhere on the board
/K10: Q13.1 (G), R64.1; also elsewhere on the board
/K11: Q14.1 (G), R67.1; also elsewhere on the board
/K12: Q15.1 (G), R70.1; also elsewhere on the board
/PP2: U10.1; also elsewhere on the board
/PP3: U11.1; also elsewhere on the board
/PP4: U12.1; also elsewhere on the board
/PP5: U14.1; also elsewhere on the board
/PP6: U15.1; also elsewhere on the board
/PP7: U16.1; also elsewhere on the board
/PP8: U17.1; also elsewhere on the board
/PP9: U19.1; also elsewhere on the board
/PP10: U20.1; also elsewhere on the board
/PP11: U21.1; also elsewhere on the board
/PP12: U22.1; also elsewhere on the board
/io2/int: C23.1, D6.3 (COM), R33.1; also elsewhere on the board
/io3/int: C24.1, D10.3 (COM), R41.1; also elsewhere on the board
/io5/int: C30.1, D16.3 (COM), R47.1; also elsewhere on the board
/io6/int: C31.1, D19.3 (COM), R50.1; also elsewhere on the board
/io7/int: C32.1, D22.3 (COM), R53.1; also elsewhere on the board
/io9/int: C36.1, D28.3 (COM), R59.1; also elsewhere on the board
/io10/int: C37.1, D31.3 (COM), R62.1; also elsewhere on the board
/io11/int: C38.1, D34.3 (COM), R65.1; also elsewhere on the board
unnamed: C23.2, R33.2, U10.7
unnamed: C24.2, R41.2, U11.7
unnamed: C25.2, R44.2, U12.7
unnamed: C30.2, R47.2, U14.7
unnamed: C31.2, R50.2, U15.7
unnamed: C32.2, R53.2, U16.7
unnamed: C33.2, R56.2, U17.7
unnamed: C36.2, R59.2, U19.7
unnamed: C37.2, R62.2, U20.7
unnamed: C38.2, R65.2, U21.7
unnamed: C39.2, R68.2, U22.7
unnamed: D42.2 (A), Q6.3 (D), U11.5
unnamed: D43.2 (A), Q7.3 (D), U12.5
unnamed: D44.2 (A), Q8.3 (D), U14.5
unnamed: D45.2 (A), Q9.3 (D), U15.5
unnamed: D46.2 (A), Q10.3 (D), U16.5
unnamed: D47.2 (A), Q11.3 (D), U17.5
unnamed: D48.2 (A), Q12.3 (D), U19.5
unnamed: D49.2 (A), Q13.3 (D), U20.5
unnamed: D50.2 (A), Q14.3 (D), U21.5
unnamed: D51.2 (A), Q15.3 (D), U22.5
VBUS: D41.1 (K), D42.1 (K), D43.1 (K), D44.1 (K), D45.1 (K), D46.1 (K), D47.1 (K), D48.1 (K), D49.1 (K), D50.1 (K), D51.1 (K), U10.3, U11.3, U12.3, U14.3, U15.3, U16.3, U17.3, U19.3, U20.3, U21.3, U22.3; also elsewhere on the board
VDD: D6.2 (K), D10.2 (K), D13.2 (K), D16.2 (K), D19.2 (K), D22.2 (K), D25.2 (K), D28.2 (K), D31.2 (K), D34.2 (K), D37.2 (K); also elsewhere on the board

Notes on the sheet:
Hammond 1455J1201BK

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
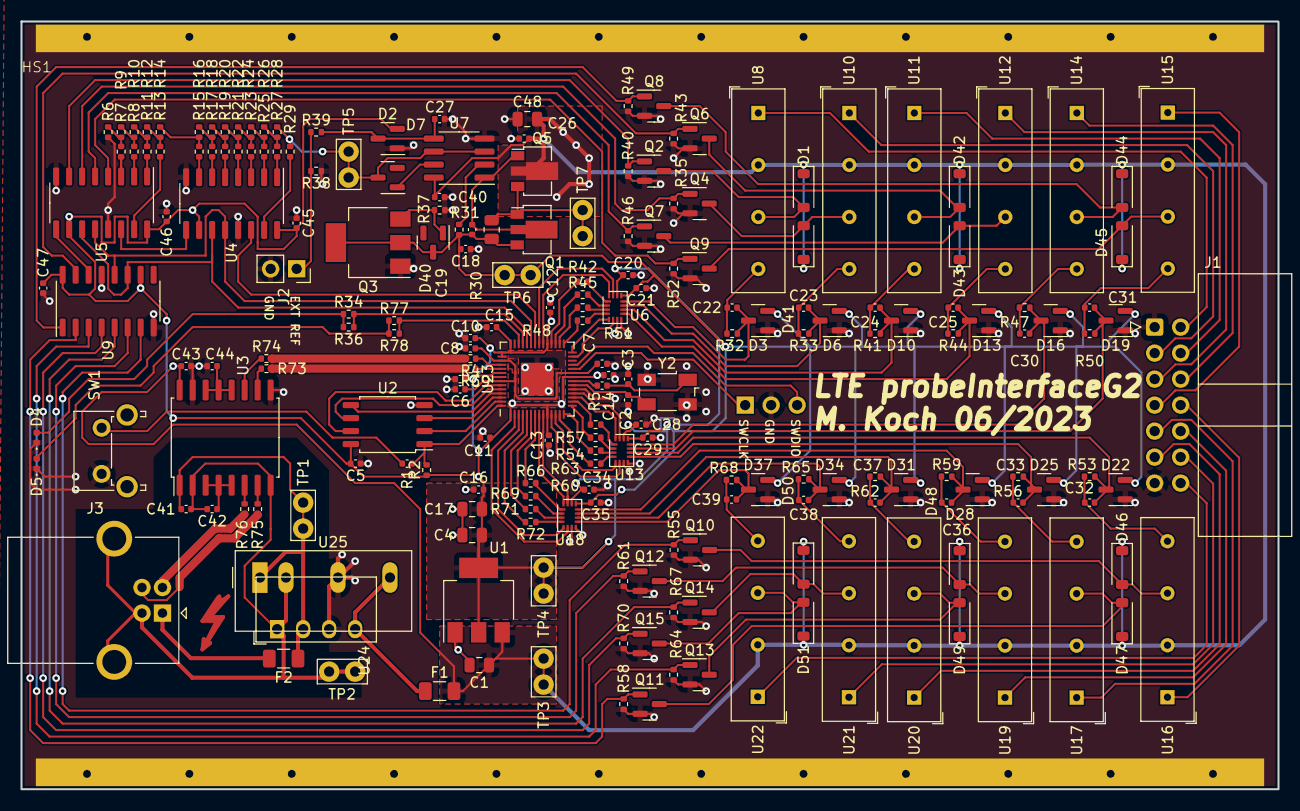
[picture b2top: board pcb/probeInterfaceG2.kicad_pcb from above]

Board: 2 copper layers, 122.8 x 75.0 mm, 212 parts (1 on the bottom side), 169 nets.

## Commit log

2022-11-12 Initial concept
2022-12-02 Added some design hints
2022-12-02 Added first firmware files
2022-12-03 moved spi example to cpp
2022-12-04 added scpi parser library
2022-12-04 added hints to submodules and moved firmware to fw
2022-12-04 scpi lib working
2022-12-04 usbtmc is working
2022-12-10 tinyusb python test working, but only with NI-VISA and not with standard linux
2022-12-10 simplified usbtmc (removed delay)
2022-12-11 usbtmc combined with scpi-parser
2022-12-11 simplified state machine for usbtmc and used scpi-parser for ieee 488.2
2022-12-17 fixed usbtmc handling multi-chunk bulkIns
2022-12-17 several changes for IEEE488.2 compliance
2022-12-18 implemented first version of spi transfer over usb
2022-12-18 added spi pin setting and boot to bootsel feature
2022-12-18 added spi baudrate setting, cpol and cpha and added boot to bootsel mode feature
2022-12-21 added simple pcb for evaluation of level shifter
2022-12-26 cleaned repo and added labels to pcbSimple
2022-12-26 updated paths to library
2022-12-28 add cs and example with gyro sensor
2022-12-29 improved l3g4200 test
2023-01-02 simplified simplePCB
2023-03-06 updated schematics for bipolar supply of opamps
2023-06-24 dropped psu part for simpler digital board, schematic and layout almost done
2023-06-25 layout done
2023-06-25 fixed drc
2023-06-25 reichelt bom added
2023-07-04 added digikey bom
2023-07-04 corrected digikey bom
2023-07-11 improved readme
2023-08-31 PCB tested and firmware adapted, gpios and spi available, readme adapted, pcbSimple removed
2023-09-27 Add example for pylabte usage
2024-03-07 added copyright notice
2024-03-07 fixed missing gpio read response
2024-03-07 fixed error in gpio read
2024-10-19 Add LICENSE
2024-10-19 added stp license
2024-10-19 removed copyrighted 3D model and replaced it with a download script
2024-10-19 removed example that requires internal python library
2024-10-19 added acknowledgment
2024-12-09 added unique id to scpi id
